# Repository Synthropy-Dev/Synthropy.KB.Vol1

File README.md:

# Synthropy.KB.Vol1
Open Source keyboard design.

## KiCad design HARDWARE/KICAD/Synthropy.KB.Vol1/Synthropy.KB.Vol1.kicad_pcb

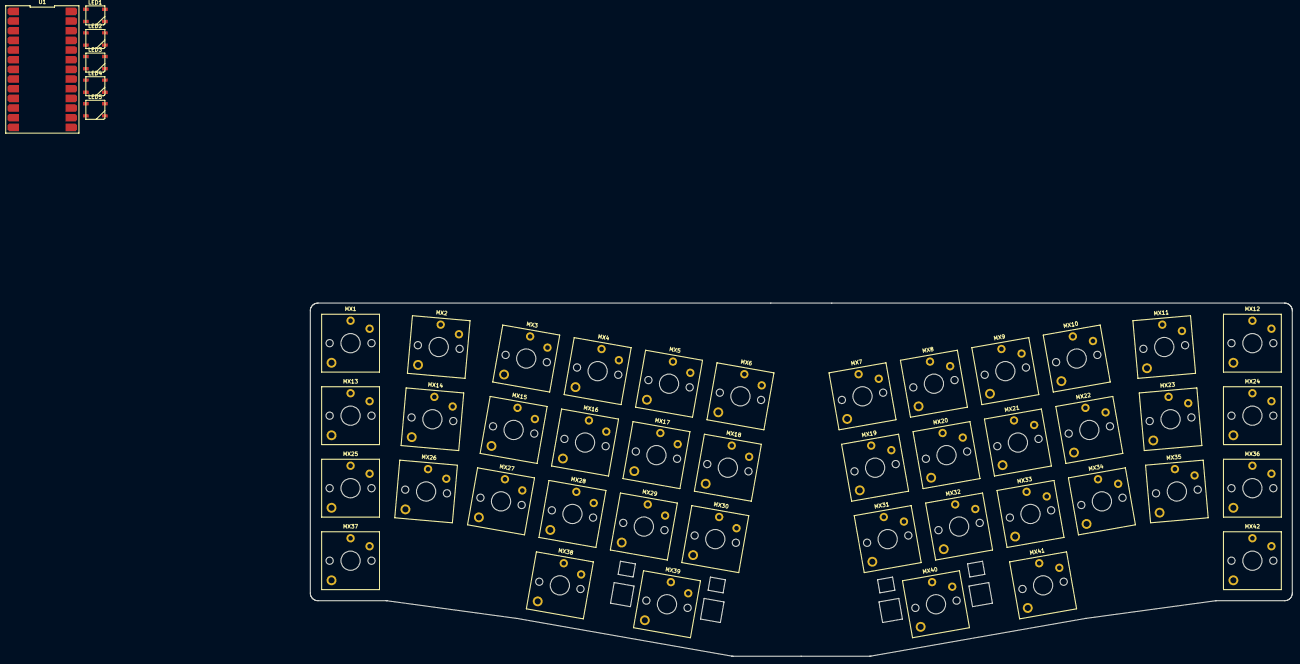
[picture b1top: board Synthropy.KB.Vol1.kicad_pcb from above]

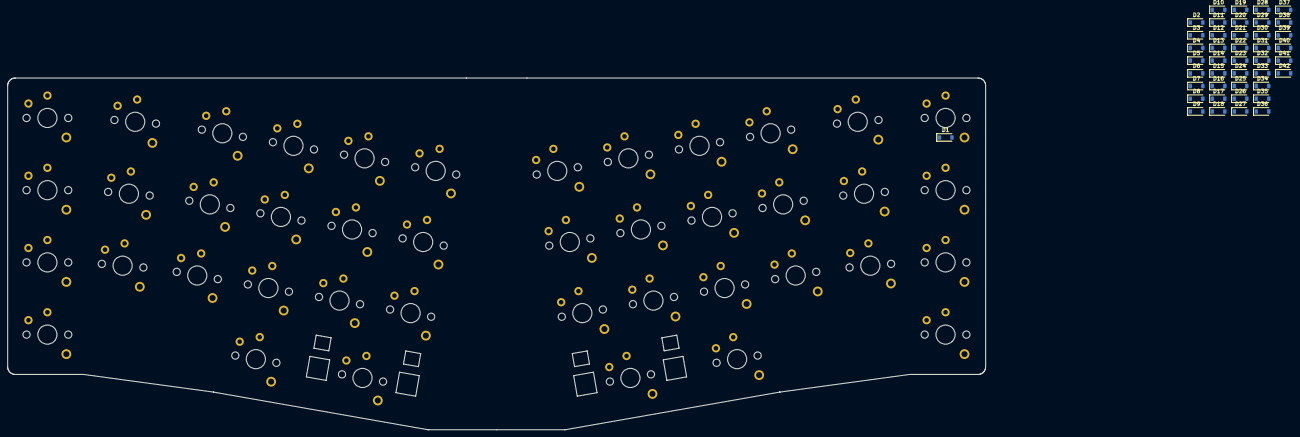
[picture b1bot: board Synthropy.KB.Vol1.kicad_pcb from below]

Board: 4 copper layers, 258.0 x 92.8 mm, 90 parts (42 on the bottom side), 51 nets, no tracks yet.

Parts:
D1, D2, D3, D4, D5, D6, D7, D8, D9, D10, D11, D12, D13, D14, D15, D16, D17, D18, D19, D20, D21, D22, D23, D24, D25, D26, D27, D28, D29, D30, D31, D32, D33, D34, D35, D36, D37, D38, D39, D40, D41, D42: D_Small; D_SOD-123
LED1, LED2, LED3, LED4, LED5: WS2812B
MX1, MX2, MX3, MX4, MX5, MX6, MX7, MX8, MX9, MX10, MX11, MX12, MX13, MX14, MX15, MX16, MX17, MX18, MX19, MX20, MX21, MX22, MX23, MX24, MX25, MX26, MX27, MX28, MX29, MX30, MX31, MX32, MX33, MX34, MX35, MX36, MX37, MX38, MX39, MX40, MX41, MX42: MX-NoLED; SW_Kailh_Choc_V1V2_1.00u
U1: kb2040; Pro-Micro

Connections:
Col0: MX1.1 (COL), MX13.1 (COL), MX25.1 (COL), MX37.1 (COL)
Col1: D13.1 (K), D14.1 (K), D15.1 (K), D16.1 (K), D17.1 (K), D18.1 (K), D19.1 (K), D20.1 (K), D21.1 (K), D22.1 (K), D23.1 (K), D24.1 (K), D25.1 (K), D26.1 (K), D27.1 (K), D28.1 (K), D29.1 (K), D30.1 (K), D31.1 (K), D32.1 (K), D33.1 (K), D34.1 (K), D35.1 (K), D36.1 (K), MX2.1 (COL), MX3.1 (COL), MX6.1 (COL), MX7.1 (COL), MX10.1 (COL), MX11.1 (COL), MX14.1 (COL), MX15.1 (COL), MX18.1 (COL), MX19.1 (COL), MX22.1 (COL), MX23.1 (COL), MX26.1 (COL), MX27.1 (COL), MX30.1 (COL), MX31.1 (COL), MX34.1 (COL), MX35.1 (COL)
Col3: MX4.1 (COL), MX16.1 (COL), MX28.1 (COL), MX38.1 (COL)
Col4: MX5.1 (COL), MX17.1 (COL), MX29.1 (COL), MX39.1 (COL)
Col7: MX8.1 (COL), MX20.1 (COL), MX32.1 (COL), MX40.1 (COL)
Col8: MX9.1 (COL), MX21.1 (COL), MX33.1 (COL), MX41.1 (COL)
Col11: MX12.1 (COL), MX24.1 (COL), MX36.1 (COL), MX42.1 (COL)
unnamed: D1.2 (A), MX1.2 (ROW)
unnamed: D2.2 (A), MX2.2 (ROW)
unnamed: D3.2 (A), MX3.2 (ROW)
unnamed: D4.2 (A), MX4.2 (ROW)
unnamed: D5.2 (A), MX5.2 (ROW)
unnamed: D6.2 (A), MX6.2 (ROW)
unnamed: D7.2 (A), MX7.2 (ROW)
unnamed: D8.2 (A), MX8.2 (ROW)
unnamed: D9.2 (A), MX9.2 (ROW)
unnamed: D10.2 (A), MX10.2 (ROW)
unnamed: D11.2 (A), MX11.2 (ROW)
unnamed: D12.2 (A), MX12.2 (ROW)
unnamed: D13.2 (A), MX13.2 (ROW)
unnamed: D14.2 (A), MX14.2 (ROW)
unnamed: D15.2 (A), MX15.2 (ROW)
unnamed: D16.2 (A), MX16.2 (ROW)
unnamed: D17.2 (A), MX17.2 (ROW)
unnamed: D18.2 (A), MX18.2 (ROW)
unnamed: D19.2 (A), MX19.2 (ROW)
unnamed: D20.2 (A), MX20.2 (ROW)
unnamed: D21.2 (A), MX21.2 (ROW)
unnamed: D22.2 (A), MX22.2 (ROW)
unnamed: D23.2 (A), MX23.2 (ROW)
unnamed: D24.2 (A), MX24.2 (ROW)
unnamed: D25.2 (A), MX25.2 (ROW)
unnamed: D26.2 (A), MX26.2 (ROW)
unnamed: D27.2 (A), MX27.2 (ROW)
unnamed: D28.2 (A), MX28.2 (ROW)
unnamed: D29.2 (A), MX29.2 (ROW)
unnamed: D30.2 (A), MX30.2 (ROW)
unnamed: D31.2 (A), MX31.2 (ROW)
unnamed: D32.2 (A), MX32.2 (ROW)
unnamed: D33.2 (A), MX33.2 (ROW)
unnamed: D34.2 (A), MX34.2 (ROW)
unnamed: D35.2 (A), MX35.2 (ROW)
unnamed: D36.2 (A), MX36.2 (ROW)
unnamed: D37.2 (A), MX37.2 (ROW)
unnamed: D38.2 (A), MX38.2 (ROW)
unnamed: D39.2 (A), MX39.2 (ROW)
unnamed: D40.2 (A), MX40.2 (ROW)
unnamed: D41.2 (A), MX41.2 (ROW)
unnamed: D42.2 (A), MX42.2 (ROW)
Row0: D1.1 (K), D2.1 (K), D3.1 (K), D4.1 (K), D5.1 (K), D6.1 (K), D7.1 (K), D8.1 (K), D9.1 (K), D10.1 (K), D11.1 (K), D12.1 (K)
Row3: D37.1 (K), D38.1 (K), D39.1 (K), D40.1 (K), D41.1 (K), D42.1 (K)

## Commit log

2024-06-14 Added layout image
2024-06-14 Created Schematic
2024-06-18 Schematic Updates
2025-05-31 Updates from prev revisions
2025-05-31 Testing Branch Feature
